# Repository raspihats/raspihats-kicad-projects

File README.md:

# raspihats-kicad-projects
raspihats KiCad projects

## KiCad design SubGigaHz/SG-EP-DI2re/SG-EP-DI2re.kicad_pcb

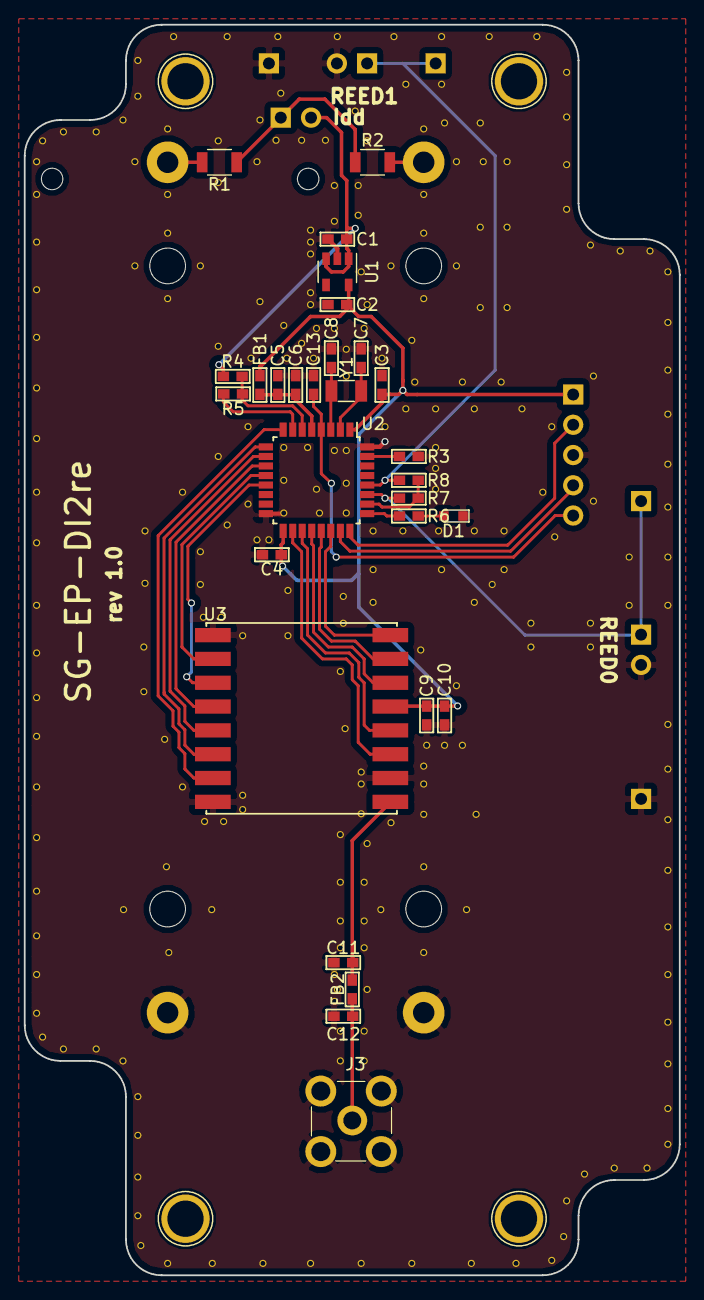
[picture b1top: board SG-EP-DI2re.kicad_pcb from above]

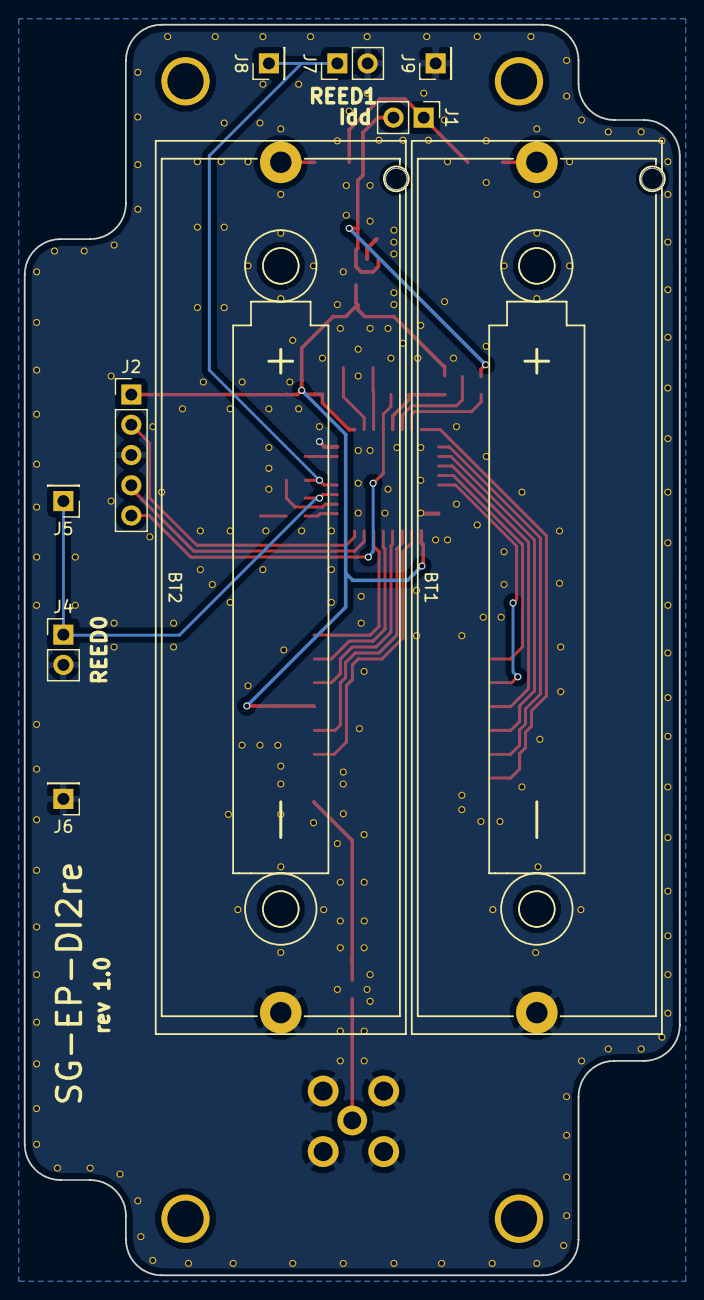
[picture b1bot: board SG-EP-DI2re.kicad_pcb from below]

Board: 2 copper layers, 55.0 x 105.0 mm, 39 parts (10 on the bottom side), 33 nets.

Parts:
BT1, BT2: NCR18650B; BHC-186501-P
C1, C2, C6: 1uF; C_0603
C3, C4, C5, C9, C11, C12, C13: 100nF; C_0603
C7, C8: 4.3pF; C_0603
C10: 10uF; C_0603
D1: LED; LED_0603
FB1, FB2: BLM18TG601TN1D; L_0603
J1: Idd; Pin_Header_Straight_1x02_Pitch2.54mm
J2: SWD; Pin_Header_Straight_1x05_Pitch2.54mm
J3: 5-1814832-1; RF_SMA_Vertical_5-1814832-1
J4: In0; Pin_Header_Straight_1x02_Pitch2.54mm
J5: In0_1; Pin_Header_Straight_1x01_Pitch2.54mm
J6: In0_2; Pin_Header_Straight_1x01_Pitch2.54mm
J7: In1; Pin_Header_Straight_1x02_Pitch2.54mm
J8: In1_1; Pin_Header_Straight_1x01_Pitch2.54mm
J9: In1_2; Pin_Header_Straight_1x01_Pitch2.54mm
R1, R2: 10; R_1206
R3: 680; R_0603
R4, R5: 47K; R_0603
R6: 10K; R_0603
R7, R8: 330K; R_0603
U1: STLQ015M33R; SOT-23-5
U2: STM32L0x1K; LQFP-32_7x7mm_Pitch0.8mm
U3: RFM9x
Y1: LFXTAL009678; Crystal_SMD_3215-2pin_3.2x1.5mm

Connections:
+BATT: C1.1, J1.2, R4.1, U1.1, U1.3
ANT1: C11.1, FB2.2, U3.9
ANT2: C12.1, FB2.1, J3.2
BOOT: R3.1, U2.31
DIO0: U2.20, U3.14
DIO1: U2.21, U3.15
DIO2: U2.22, U3.16
DIO3: U2.18, U3.11
DIO4: U2.19, U3.12
DIO5: U2.8, U3.7
GND: BT1.2, BT2.2, C1.2, C2.2, C3.2, C4.2, C5.2, C6.2, C7.1, C8.1, C9.2, C10.2, C11.2, C12.2, C13.2, D1.1, J2.3, J3.1, J4.2, J6.1, J7.2, J9.1, R3.2, U1.2, U2.16, U2.32, U3.1, U3.8, U3.10
LED: R6.1, U2.25
MISO: U2.12, U3.2
MOSI: U2.13, U3.3
NRST: C13.1, J2.5, U2.4
NSS: U2.10, U3.5
unnamed: BT1.1, R1.2
unnamed: BT2.1, R2.2
unnamed: D1.2, R6.2
unnamed: J1.1, R1.1, R2.1
OSC32_IN: C7.2, U2.2, Y1.2
OSC32_OUT: C8.2, U2.3, Y1.1
REED_EN: R7.1, R8.1, U2.26
REED_IN0: J4.1, J5.1, R7.2, U2.27
REED_IN1: J7.1, J8.1, R8.2, U2.28
RESET: U2.9, U3.6
SCK: U2.11, U3.4
SWCLK: J2.2, U2.24
SWDIO: J2.4, U2.23
VBAT_DIV: R4.2, R5.1, U2.6
VBAT_DIV_EN: R5.2, U2.7
VDD: C2.1, C3.1, C4.1, C9.1, C10.1, FB1.2, J2.1, U1.5, U2.1, U2.17, U3.13
VDDA: C5.1, C6.1, FB1.1, U2.5

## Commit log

2018-03-25 aded SubGigaHz(LoRa) EndPoint with 2 Reed Digital Input channels
